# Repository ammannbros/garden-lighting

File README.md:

# Building

* Install *Python 3*
* Check out this repo and run `python setup.py build && python setup.py sdist`.

# Deploy

`scp dist/garden-lighting-0.2.tar.gz pi@ammann.dyn.maxammann.org:`

# Running using virtualenv

* Install *virtualenv* for *Python 3*
* Check out this repo and run `virtualenv dev-env`
* Activate by running `source dev-env/bin/activate`
* Install by running `python setup.py develop`
* Run `garden-lighting`. That's it!

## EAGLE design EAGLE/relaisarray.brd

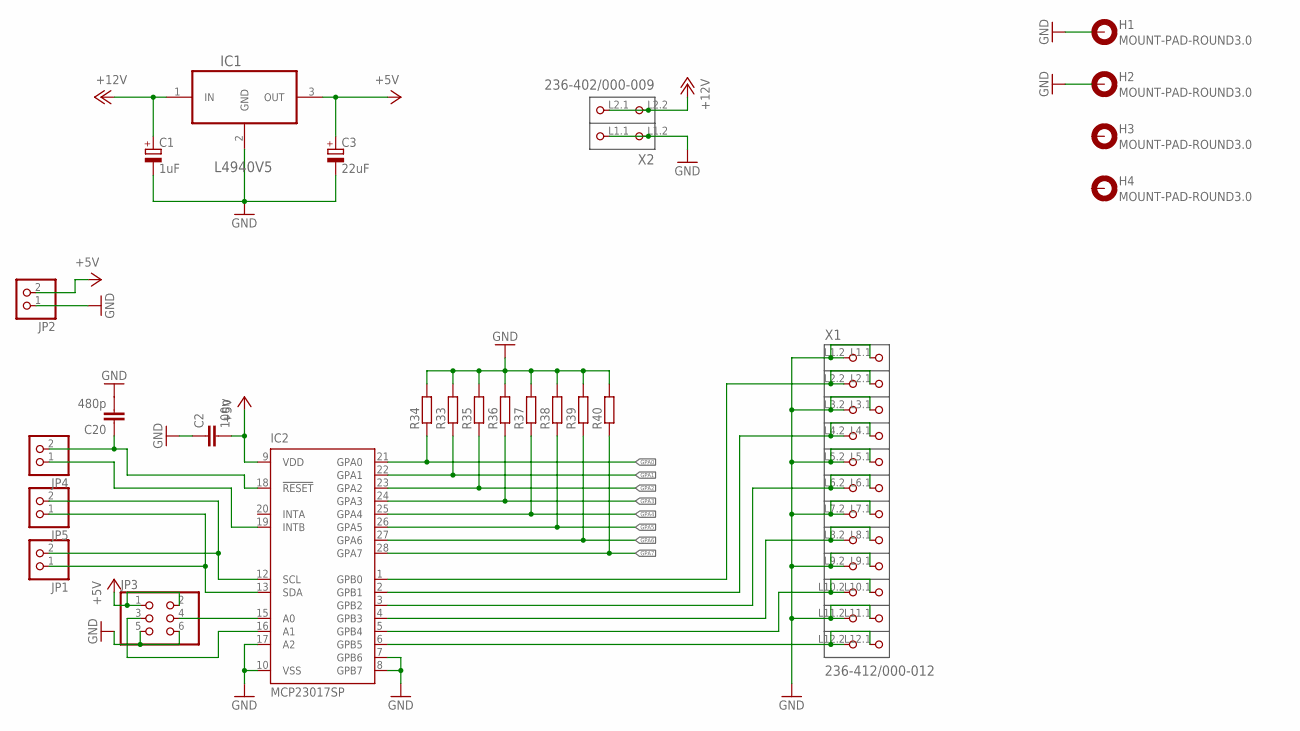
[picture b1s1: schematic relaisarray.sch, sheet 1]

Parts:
C1: 1uF; TT2D5
C2: 100n; C050-035X075
C3: 22uF; TT2D5
C20: 480p; C050-035X075
H1, H2, H3, H4: MOUNT-PAD-ROUND3.0; 3,0-PAD
IC1: L4940V5; TO254P482X1024X3124-3P
IC2: MCP23017SP; DIL28-3
JP1, JP2, JP4, JP5: PINHD-1X2; 1X02
JP3: PINHD-2X3; 2X03
R33, R34, R35, R36, R37, R38, R39, R40: R-EU_0207/10; 0207/10
X1: 236-412/000-012; P-236-412
X2: 236-402/000-009; P-236-402

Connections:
+5V: C2.2, C3.+, IC1.3 (OUT), IC2.9 (VDD), JP2.2, JP3.1, JP3.2; also elsewhere on the board
+12V: C1.+, IC1.1 (IN), X2.L2.1 (P2.1), X2.L2.2 (P2.2); also elsewhere on the board
GND: C1.-, C2.1, C3.-, C20.2, H1.B3,0, H2.B3,0, IC1.2 (GND), IC2.7 (GPB6), IC2.8 (GPB7), IC2.10 (VSS), IC2.17 (A2), JP2.1, JP3.5, JP3.6, R33.2, R34.2, R35.2, R36.2, R37.2, R38.2, R39.2, R40.2, X1.L1.1 (P1.1), X1.L1.2 (P1.2), X1.L3.1 (P3.1), X1.L3.2 (P3.2), X1.L5.1 (P5.1), X1.L5.2 (P5.2), X1.L7.1 (P7.1), X1.L7.2 (P7.2), X1.L9.1 (P9.1), X1.L9.2 (P9.2), X1.L11.1 (P11.1), X1.L11.2 (P11.2), X2.L1.1 (P1.1), X2.L1.2 (P1.2); also elsewhere on the board
GPA0: IC2.21 (GPA0), R34.1; also elsewhere on the board
GPA1: IC2.22 (GPA1), R33.1; also elsewhere on the board
GPA2: IC2.23 (GPA2), R35.1; also elsewhere on the board
GPA3: IC2.24 (GPA3), R36.1; also elsewhere on the board
GPA4: IC2.25 (GPA4), R37.1; also elsewhere on the board
GPA5: IC2.26 (GPA5), R38.1; also elsewhere on the board
GPA6: IC2.27 (GPA6), R39.1; also elsewhere on the board
GPA7: IC2.28 (GPA7), R40.1; also elsewhere on the board
INTB: IC2.19 (INTB), JP4.1
unnamed: IC2.16 (A1), JP3.3
unnamed: IC2.15 (A0), JP3.4
unnamed: IC2.6 (GPB5), X1.L12.1 (P12.1), X1.L12.2 (P12.2)
unnamed: IC2.5 (GPB4), X1.L10.1 (P10.1), X1.L10.2 (P10.2)
unnamed: IC2.4 (GPB3), X1.L8.1 (P8.1), X1.L8.2 (P8.2)
unnamed: IC2.3 (GPB2), X1.L6.1 (P6.1), X1.L6.2 (P6.2)
unnamed: IC2.2 (GPB1), X1.L4.1 (P4.1), X1.L4.2 (P4.2)
unnamed: IC2.1 (GPB0), X1.L2.1 (P2.1), X1.L2.2 (P2.2)
RESET: C20.1, IC2.18 (!RESET), JP4.2
SCL: IC2.12 (SCL), JP1.2, JP5.2
SDA: IC2.13 (SDA), JP1.1, JP5.1

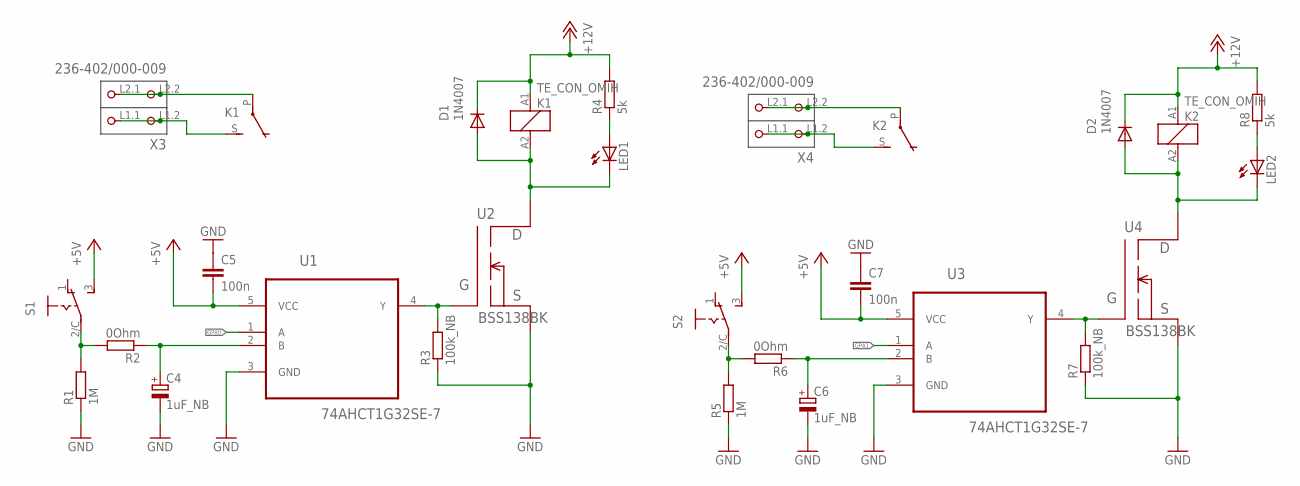
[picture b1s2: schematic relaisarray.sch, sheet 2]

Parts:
C4, C6: 1uF_NB; TT2D5
C5, C7: 100n; C050-035X075
D1, D2: 1N4007; DO41-10
K1, K2: TE_CON_OMIH
LED1, LED2: LED5MM
R1, R5: 1M; 0207/10
R2, R6: 0Ohm; 0207/10
R3, R7: 100k_NB; 0207/10
R4, R8: 5k; 0207/10
S1, S2: OS102011MS2QS1
U1, U3: 74AHCT1G32SE-7; SOT65P210X110-5N
U2, U4: BSS138BK; SOT65P210X110-3N
X3, X4: 236-402/000-009; P-236-402

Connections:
+5V: C5.2, C7.2, S1.3, S2.3, U1.5 (VCC), U3.5 (VCC); also elsewhere on the board
+12V: D1.C, D2.C, K1.A1, K2.A1, R4.2, R8.2; also elsewhere on the board
GND: C4.-, C5.1, C6.-, C7.1, R1.1, R3.1, R5.1, R7.1, U1.3 (GND), U2.2 (S), U3.3 (GND), U4.2 (S); also elsewhere on the board
GPA0: U1.1 (A); also elsewhere on the board
GPA1: U3.1 (A); also elsewhere on the board
unnamed: R3.2, U1.4 (Y), U2.1 (G)
unnamed: LED1.A, R4.1
unnamed: D1.A, K1.A2, LED1.K (C), U2.3 (D)
unnamed: R1.2, R2.2, S1.2/C
unnamed: K1.P, X3.L2.1 (P2.1), X3.L2.2 (P2.2)
unnamed: K1.S, X3.L1.1 (P1.1), X3.L1.2 (P1.2)
unnamed: C4.+, R2.1, U1.2 (B)
unnamed: R7.2, U3.4 (Y), U4.1 (G)
unnamed: LED2.A, R8.1
unnamed: D2.A, K2.A2, LED2.K (C), U4.3 (D)
unnamed: R5.2, R6.2, S2.2/C
unnamed: K2.P, X4.L2.1 (P2.1), X4.L2.2 (P2.2)
unnamed: K2.S, X4.L1.1 (P1.1), X4.L1.2 (P1.2)
unnamed: C6.+, R6.1, U3.2 (B)

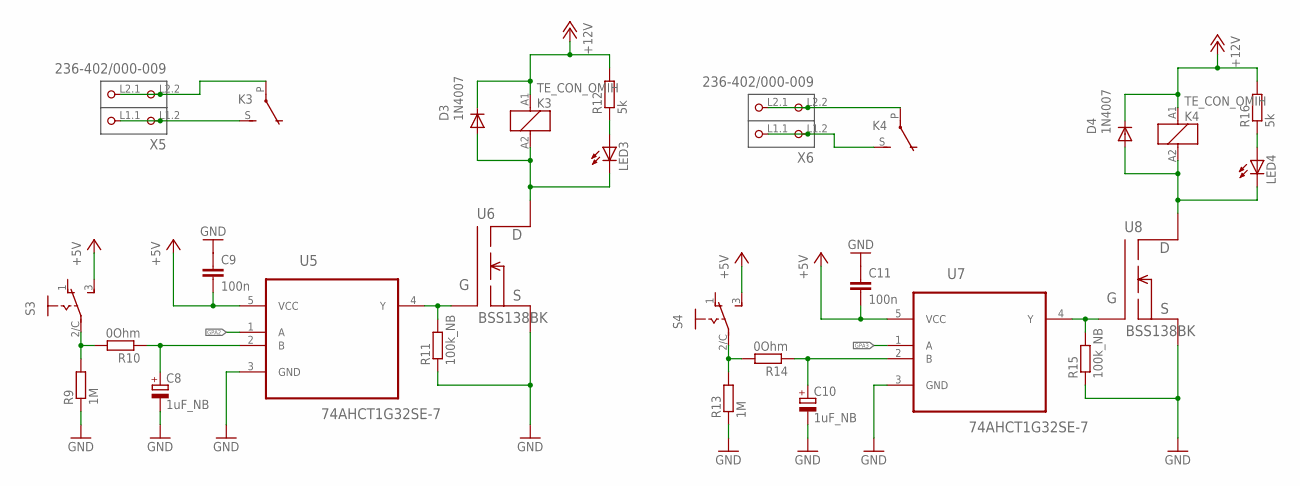
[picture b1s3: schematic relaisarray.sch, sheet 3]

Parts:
C8, C10: 1uF_NB; TT2D5
C9, C11: 100n; C050-035X075
D3, D4: 1N4007; DO41-10
K3, K4: TE_CON_OMIH
LED3, LED4: LED5MM
R9, R13: 1M; 0207/10
R10, R14: 0Ohm; 0207/10
R11, R15: 100k_NB; 0207/10
R12, R16: 5k; 0207/10
S3, S4: OS102011MS2QS1
U5, U7: 74AHCT1G32SE-7; SOT65P210X110-5N
U6, U8: BSS138BK; SOT65P210X110-3N
X5, X6: 236-402/000-009; P-236-402

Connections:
+5V: C9.2, C11.2, S3.3, S4.3, U5.5 (VCC), U7.5 (VCC); also elsewhere on the board
+12V: D3.C, D4.C, K3.A1, K4.A1, R12.2, R16.2; also elsewhere on the board
GND: C8.-, C9.1, C10.-, C11.1, R9.1, R11.1, R13.1, R15.1, U5.3 (GND), U6.2 (S), U7.3 (GND), U8.2 (S); also elsewhere on the board
GPA2: U5.1 (A); also elsewhere on the board
GPA3: U7.1 (A); also elsewhere on the board
unnamed: R11.2, U5.4 (Y), U6.1 (G)
unnamed: LED3.A, R12.1
unnamed: D3.A, K3.A2, LED3.K (C), U6.3 (D)
unnamed: R9.2, R10.2, S3.2/C
unnamed: K3.P, X5.L2.1 (P2.1), X5.L2.2 (P2.2)
unnamed: K3.S, X5.L1.1 (P1.1), X5.L1.2 (P1.2)
unnamed: C8.+, R10.1, U5.2 (B)
unnamed: R15.2, U7.4 (Y), U8.1 (G)
unnamed: LED4.A, R16.1
unnamed: D4.A, K4.A2, LED4.K (C), U8.3 (D)
unnamed: R13.2, R14.2, S4.2/C
unnamed: K4.P, X6.L2.1 (P2.1), X6.L2.2 (P2.2)
unnamed: K4.S, X6.L1.1 (P1.1), X6.L1.2 (P1.2)
unnamed: C10.+, R14.1, U7.2 (B)

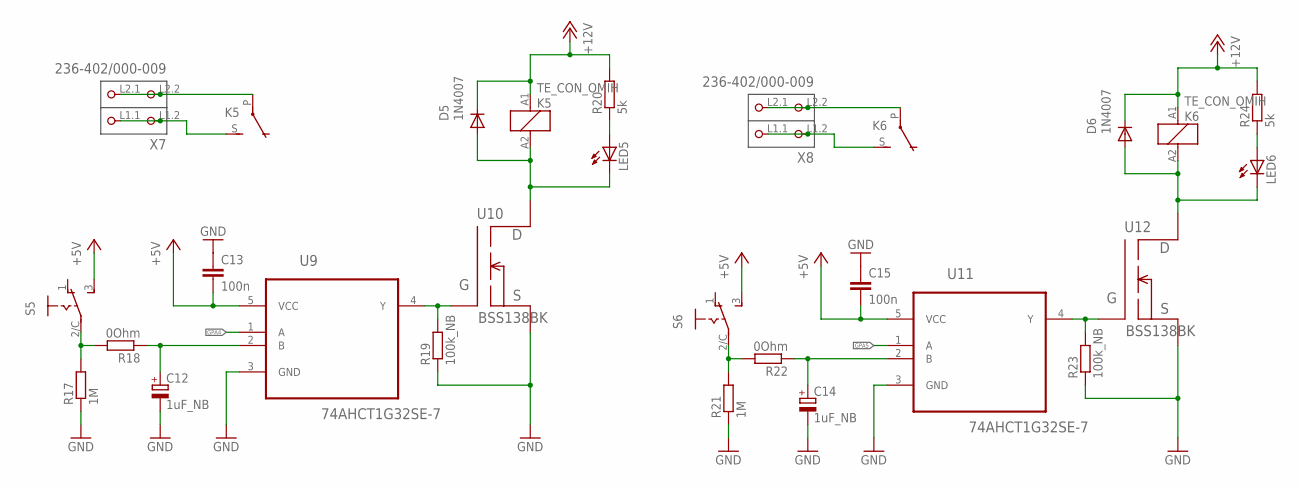
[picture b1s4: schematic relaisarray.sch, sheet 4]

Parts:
C12, C14: 1uF_NB; TT2D5
C13, C15: 100n; C050-035X075
D5, D6: 1N4007; DO41-10
K5, K6: TE_CON_OMIH
LED5, LED6: LED5MM
R17, R21: 1M; 0207/10
R18, R22: 0Ohm; 0207/10
R19, R23: 100k_NB; 0207/10
R20, R24: 5k; 0207/10
S5, S6: OS102011MS2QS1
U9, U11: 74AHCT1G32SE-7; SOT65P210X110-5N
U10, U12: BSS138BK; SOT65P210X110-3N
X7, X8: 236-402/000-009; P-236-402

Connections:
+5V: C13.2, C15.2, S5.3, S6.3, U9.5 (VCC), U11.5 (VCC); also elsewhere on the board
+12V: D5.C, D6.C, K5.A1, K6.A1, R20.2, R24.2; also elsewhere on the board
GND: C12.-, C13.1, C14.-, C15.1, R17.1, R19.1, R21.1, R23.1, U9.3 (GND), U10.2 (S), U11.3 (GND), U12.2 (S); also elsewhere on the board
GPA4: U9.1 (A); also elsewhere on the board
GPA5: U11.1 (A); also elsewhere on the board
unnamed: R19.2, U9.4 (Y), U10.1 (G)
unnamed: LED5.A, R20.1
unnamed: D5.A, K5.A2, LED5.K (C), U10.3 (D)
unnamed: R17.2, R18.2, S5.2/C
unnamed: K5.P, X7.L2.1 (P2.1), X7.L2.2 (P2.2)
unnamed: K5.S, X7.L1.1 (P1.1), X7.L1.2 (P1.2)
unnamed: C12.+, R18.1, U9.2 (B)
unnamed: R23.2, U11.4 (Y), U12.1 (G)
unnamed: LED6.A, R24.1
unnamed: D6.A, K6.A2, LED6.K (C), U12.3 (D)
unnamed: R21.2, R22.2, S6.2/C
unnamed: K6.P, X8.L2.1 (P2.1), X8.L2.2 (P2.2)
unnamed: K6.S, X8.L1.1 (P1.1), X8.L1.2 (P1.2)
unnamed: C14.+, R22.1, U11.2 (B)

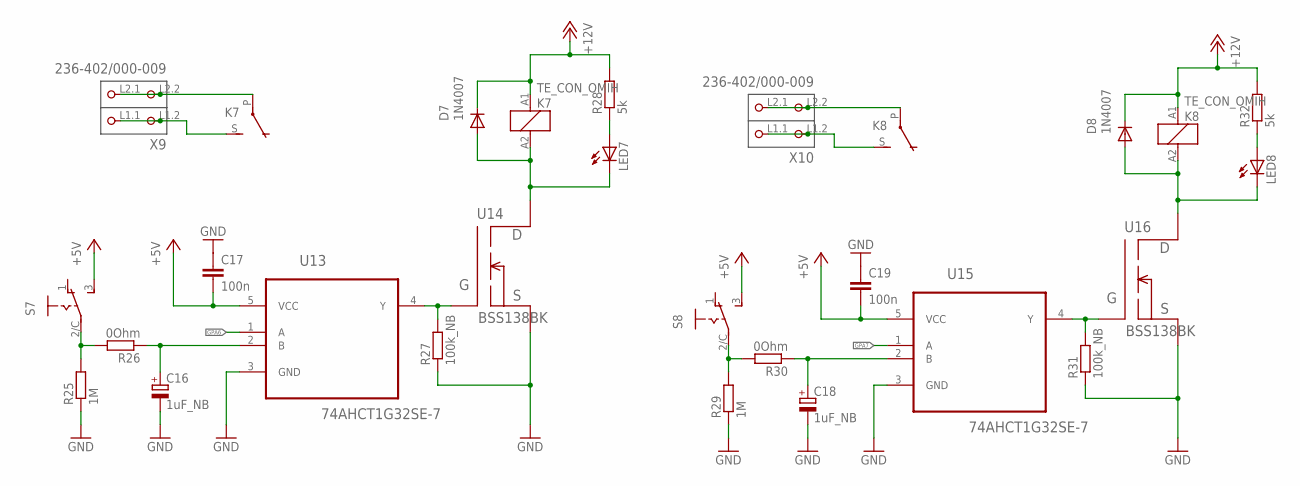
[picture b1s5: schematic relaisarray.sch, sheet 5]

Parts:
C16, C18: 1uF_NB; TT2D5
C17, C19: 100n; C050-035X075
D7, D8: 1N4007; DO41-10
K7, K8: TE_CON_OMIH
LED7, LED8: LED5MM
R25, R29: 1M; 0207/10
R26, R30: 0Ohm; 0207/10
R27, R31: 100k_NB; 0207/10
R28, R32: 5k; 0207/10
S7, S8: OS102011MS2QS1
U13, U15: 74AHCT1G32SE-7; SOT65P210X110-5N
U14, U16: BSS138BK; SOT65P210X110-3N
X9, X10: 236-402/000-009; P-236-402

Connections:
+5V: C17.2, C19.2, S7.3, S8.3, U13.5 (VCC), U15.5 (VCC); also elsewhere on the board
+12V: D7.C, D8.C, K7.A1, K8.A1, R28.2, R32.2; also elsewhere on the board
GND: C16.-, C17.1, C18.-, C19.1, R25.1, R27.1, R29.1, R31.1, U13.3 (GND), U14.2 (S), U15.3 (GND), U16.2 (S); also elsewhere on the board
GPA6: U13.1 (A); also elsewhere on the board
GPA7: U15.1 (A); also elsewhere on the board
unnamed: R27.2, U13.4 (Y), U14.1 (G)
unnamed: LED7.A, R28.1
unnamed: D7.A, K7.A2, LED7.K (C), U14.3 (D)
unnamed: R25.2, R26.2, S7.2/C
unnamed: K7.P, X9.L2.1 (P2.1), X9.L2.2 (P2.2)
unnamed: K7.S, X9.L1.1 (P1.1), X9.L1.2 (P1.2)
unnamed: C16.+, R26.1, U13.2 (B)
unnamed: R31.2, U15.4 (Y), U16.1 (G)
unnamed: LED8.A, R32.1
unnamed: D8.A, K8.A2, LED8.K (C), U16.3 (D)
unnamed: R29.2, R30.2, S8.2/C
unnamed: K8.P, X10.L2.1 (P2.1), X10.L2.2 (P2.2)
unnamed: K8.S, X10.L1.1 (P1.1), X10.L1.2 (P1.2)
unnamed: C18.+, R30.1, U15.2 (B)

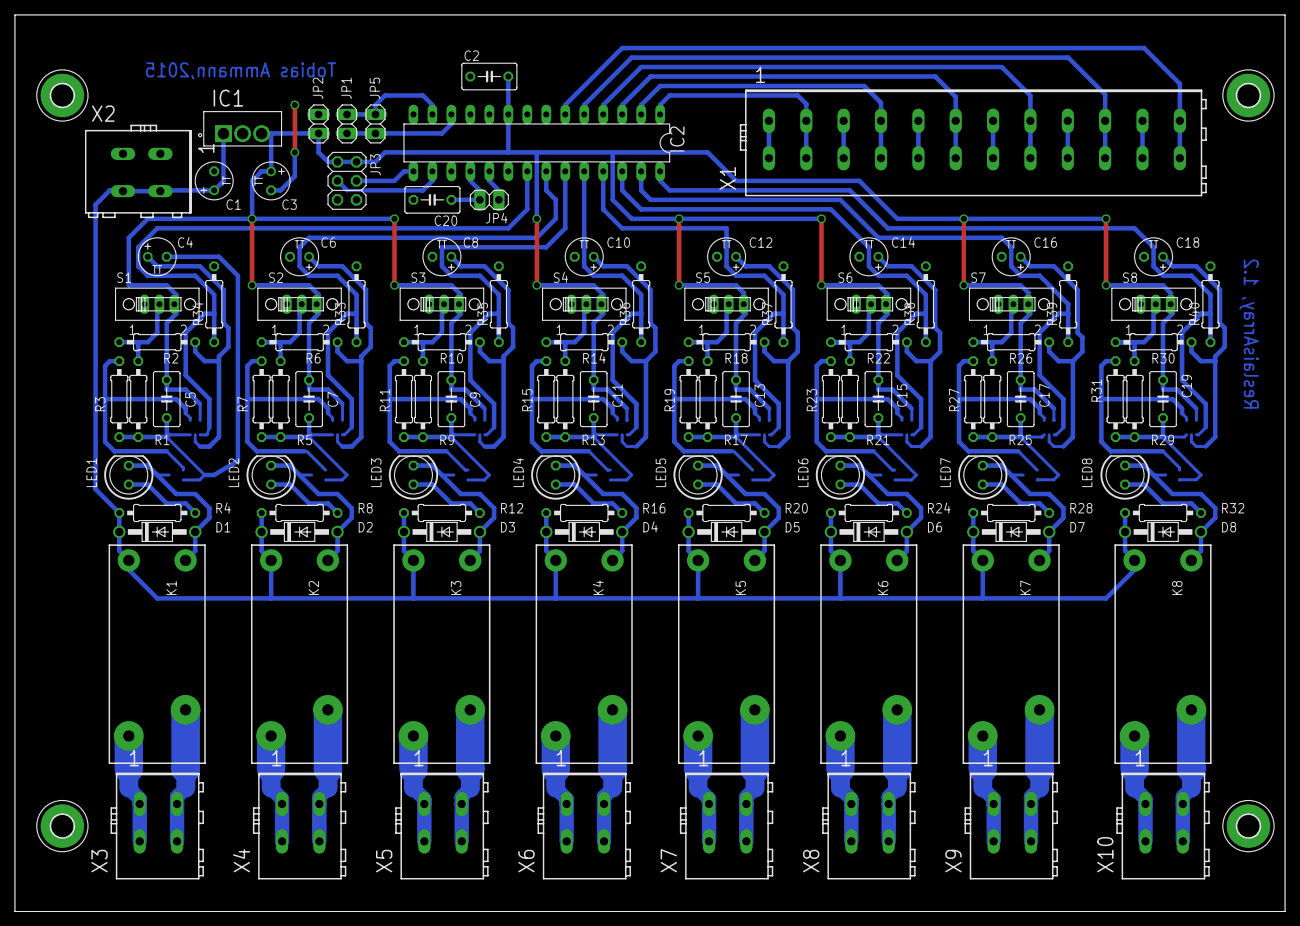
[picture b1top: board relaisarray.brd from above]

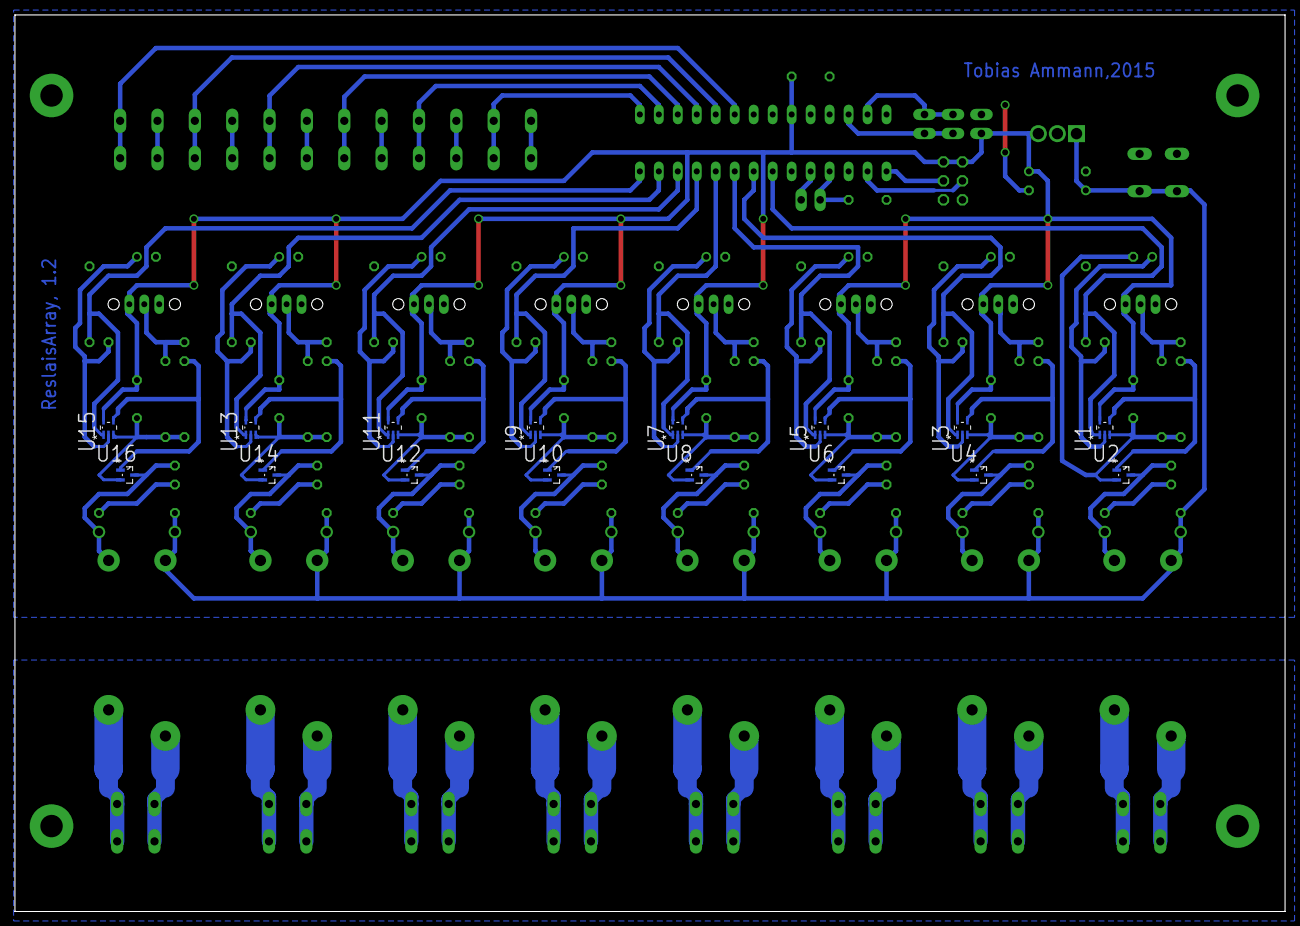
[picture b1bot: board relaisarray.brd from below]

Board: 2 copper layers, 170.0 x 120.0 mm, 129 parts (16 on the bottom side), 79 nets.

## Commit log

2015-04-19 Second commit
2015-04-20 First commit MCP23017 library
    first test pending
2015-04-20 Test file updated
2015-04-20 0 = true in python
2015-04-20 First Methods implemented and tested
    write a,b
    ioconfig a,b
    read a,b
    INPUT POLARITY REGISTER
2015-04-20 First Methods implemented and tested
    write a,b
    ioconfig a,b
    read a,b
    INPUT POLARITY REGISTER
    fixed compiler error
2015-04-20 First Methods implemented and tested
    write a,b
    ioconfig a,b
    read a,b
    INPUT POLARITY REGISTER
    some comments
2015-04-20 test
2015-04-21 Added deploy instructions
2015-04-21 Added setup.py with dependency instructions
2015-04-21 Added "binary" main script
2015-04-21 Added web framework skeleton
2015-04-21 src is a package now. Should probably be renamed to "garden-lighting" or removed
2015-04-21 Updated .gitignore
2015-04-22 Added sass support
2015-04-22 Refactored src -> garden_lighting
2015-04-23 MCP23017 lbr final but NOT tested
2015-04-23 added main for test purpose
2015-04-23 MCP23017 final and tested
2015-04-23 Added RPi.GPIO depencendy
2015-04-23 Added device handler and scheduler
2015-04-23 lightControl compleded and tested
2015-04-24 Refactor project and give it a first glance
2015-04-25 Added basic font-end light control and schedule settings, also using bower now
2015-04-25 Removed unnecessary panel
2015-04-26 added complete initialisation added read methods for interrupts
2015-04-26 fixed error block data <-> byte data
2015-04-26 Added short discription of the class
2015-04-26 Fixed time selection
2015-04-28 Using a list view now, added rules view
2015-04-30 Dynamic building of html sites, ui overhaul
2015-04-30 Added config file
2015-05-01 Added rules
2015-05-01 Packing resources, added favicon
2015-05-02 Beautify rules and redirect after finishing
2015-05-04 Made controls fool-prove
2015-05-04 Display summary text; batch on/off for devices; remove rules; first real config.py
2015-05-04 Fixed horizontal over-width
2015-05-09 Updated config; port -> 80; fixed time selection
2015-05-13 Added start parameters, easier configuration, rules are now persistent
2015-05-13 beautify button group
2015-05-13 renamed lightControl and added dummy
2015-05-14 Refactored using blueprints
2015-05-14 Started work on scheduling, implementing automatic and manual mode
2015-05-15 manual/automatic is now handled by the device ifself
2015-05-15 You could say manual and automatic mod is handled pretty neat now
2015-05-15 Working on a display for the next action by time
2015-05-16 Reformatted light_control, added get_lights
2015-05-16 Switching is now done by a separate thread if the user spams the server; todo: merge scheduling threads, merge light_control and light_scheduler
2015-05-17 Extracted gpio functionality from MCP23017
2015-05-17 Merged light_control and scheduler, using one thread for all scheduling, saving using pickle, api interface to get all information about every device and rule
2015-05-18 Fixed logging, added web log, fixed light_control
2015-05-19 lights update not async and automatically
2015-05-20 fixed missing call to update_switched
2015-05-22 Added timer and refresh button
2015-05-22 Reload on countdown finish, shorten format
2015-05-22 Read log from file
2015-05-22 Calculate correct next action by using the actual exact date
2015-05-22 Format log
2015-05-26 Fixed sorting bug and bug when trying to disable for a specific time
2015-05-28 Basic code for temperature receiving
2015-05-28 Using pigpio for the moment
2015-06-08 Updated config and beatified frontend
2015-06-09 Cleanup and using wiringpi 2
2015-06-17 Fixed rules for device groups, using wiringpi sysfs
2015-06-23 Added temperature reading for testing
2015-07-13 EAGLE
2015-07-13 PICS
2015-07-13 Create gh-pages branch via GitHub
2015-07-13 bilder verkleinert
2015-08-24 Added android app
2015-11-07 Updated temperatures
2015-11-28 Fixed light on/off switching
2016-05-28 Using tinydb for storage
2017-12-03 Use wiringpi instead of wiringpi2
2019-04-21 Use wiringPiSetupGpio, which required root. With wiringPiSetupSys some gpios stayed on low after boot.
2019-04-21 Replace sass with css
2019-04-21 Use css instead of sass
2019-04-21 Add docu about bower
2019-04-21 Upgrade dependencies
2022-12-25 Remove wiringpi dependency
2022-12-25 Remove sass dependency
2022-12-25 Remove script dependency
2022-12-25 Update project setup
2022-12-25 Fix bower setup
2022-12-25 Update gitignore
2022-12-25 Fix gitignore
2022-12-25 Remove click again
2022-12-25 Fix GPIO interaction
2022-12-25 Add images
2022-12-25 Add Relaisarray
2022-12-25 Add temperature plot via netdata
2022-12-25 Rever dry
2023-07-16 Disable tiny db
2024-10-31 Fix flask 2 install by setting werkzeug version
2024-10-31 Update flask
